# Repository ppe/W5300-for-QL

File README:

Hardware design and drivers for Sinclair QL experimental ethernet card.

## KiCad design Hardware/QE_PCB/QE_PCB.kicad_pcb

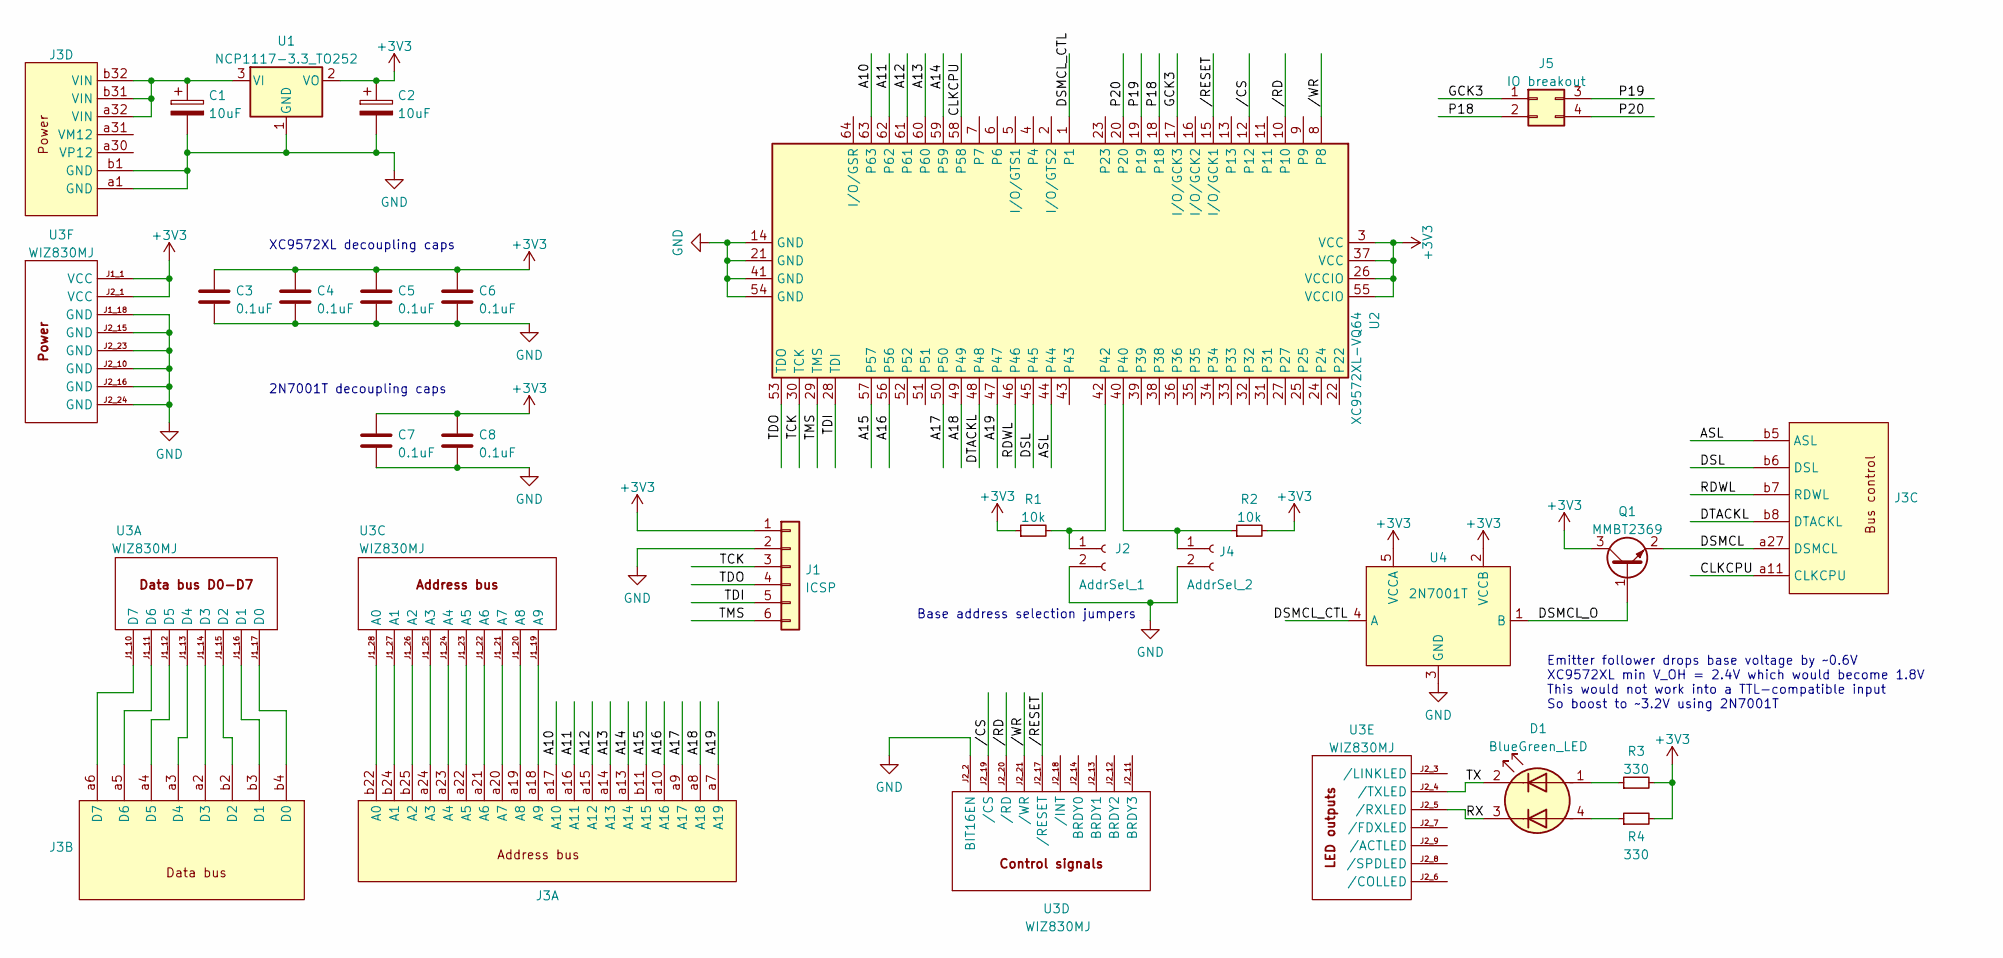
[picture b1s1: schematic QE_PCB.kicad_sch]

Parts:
C1, C2: 10uF; CP_EIA-6032-20_AVX-F_Pad2.25x2.35mm_HandSolder
C3, C4, C5, C6, C7, C8: 0.1uF; C_0603_1608Metric_Pad1.08x0.95mm_HandSolder
D1: BlueGreen_LED; LED_Dual_BG_2.0x1.25_Kingbright
J1: ICSP; PinHeader_1x06_P2.54mm_Vertical
J2: AddrSel_1; PinHeader_1x02_P2.54mm_Vertical
J3: Expansion_connector; DIN41612_B_2x32_Female_Horizontal_THT
J4: AddrSel_2; PinHeader_1x02_P2.54mm_Vertical
J5: IO breakout; PinHeader_1x04_P2.54mm_Vertical
Q1: MMBT2369; SOT-23
R1, R2: 10k; R_0805_2012Metric_Pad1.20x1.40mm_HandSolder
R3, R4: 330; R_0805_2012Metric_Pad1.20x1.40mm_HandSolder
U1: NCP1117-3.3_TO252; NCP1117 TO-252-2
U2: XC9572XL-VQ64; TQFP-64_10x10mm_P0.5mm
U3: WIZ830MJ
U4: 2N7001T; SOT-353_SC-70-5_Handsoldering

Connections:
+3V3: C2.1, C3.1, C4.1, C5.1, C6.1, C7.1, C8.1, J1.1, Q1.3 (C), R1.1, R2.2, R3.2, R4.2, U1.2 (VO), U2.3 (VCC), U2.26 (VCCIO), U2.37 (VCC), U2.55 (VCCIO), U3.J1_1 (VCC), U3.J2_1 (VCC), U4.2 (VCCB), U4.5 (VCCA)
/A10: J3.a17 (A10), U2.63
/A11: J3.a16 (A11), U2.62
/A12: J3.a15 (A12), U2.61
/A13: J3.a14 (A13), U2.60
/A14: J3.a13 (A14), U2.59
/A15: J3.b11 (A15), U2.57
/A16: J3.a10 (A16), U2.56
/A17: J3.a9 (A17), U2.50
/A18: J3.a8 (A18), U2.49
/A19: J3.a7 (A19), U2.47
/ASL: J3.b5 (ASL), U2.44
/CLKCPU: J3.a11 (CLKCPU), U2.58
/DSL: J3.b6 (DSL), U2.45
/DSMCL: J3.a27 (DSMCL), Q1.2 (E)
/DSMCL_CTL: U2.1, U4.4 (A)
/DSMCL_O: Q1.1 (B), U4.1 (B)
/DTACKL: J3.b8 (DTACKL), U2.48
/GCK3: J5.1, U2.17 (I/O/GCK3)
/P18: J5.2, U2.18
/P19: J5.3, U2.19
/P20: J5.4, U2.20
/RDWL: J3.b7 (RDWL), U2.46
/RX: D1.3 (K2), U3.J2_5 (/RXLED)
/TCK: J1.3, U2.30 (TCK)
/TDI: J1.5, U2.28 (TDI)
/TDO: J1.4, U2.53 (TDO)
/TMS: J1.6, U2.29 (TMS)
/TX: D1.2 (K1), U3.J2_4 (/TXLED)
//CS: U2.12, U3.J2_19 (/CS)
//RD: U2.10, U3.J2_20 (/RD)
//RESET: U2.15 (I/O/GCK1), U3.J2_17 (/RESET)
//WR: U2.8, U3.J2_21 (/WR)
GND: C1.2, C2.2, C3.2, C4.2, C5.2, C6.2, C7.2, C8.2, J1.2, J2.2, J3.a1 (GND), J3.b1 (GND), J4.2, U1.1 (GND), U2.14 (GND), U2.21 (GND), U2.41 (GND), U2.54 (GND), U3.J1_18 (GND), U3.J2_2 (BIT16EN), U3.J2_10 (GND), U3.J2_15 (GND), U3.J2_16 (GND), U3.J2_23 (GND), U3.J2_24 (GND), U4.3 (GND)
unnamed: C1.1, J3.a32 (VIN), J3.b31 (VIN), J3.b32 (VIN), U1.3 (VI)
unnamed: D1.1 (A1), R3.1
unnamed: D1.4 (A2), R4.1
unnamed: J2.1, R1.2, U2.42
unnamed: J3.a2 (D3), U3.J1_14 (D3)
unnamed: J3.a3 (D4), U3.J1_13 (D4)
unnamed: J3.a4 (D5), U3.J1_12 (D5)
unnamed: J3.a5 (D6), U3.J1_11 (D6)
unnamed: J3.a6 (D7), U3.J1_10 (D7)
unnamed: J3.a18 (A9), U3.J1_19 (A9)
unnamed: J3.a19 (A8), U3.J1_20 (A8)
unnamed: J3.a20 (A7), U3.J1_21 (A7)
unnamed: J3.a21 (A6), U3.J1_22 (A6)
unnamed: J3.a22 (A5), U3.J1_23 (A5)
unnamed: J3.a23 (A4), U3.J1_24 (A4)
unnamed: J3.a24 (A3), U3.J1_25 (A3)
unnamed: J3.b2 (D2), U3.J1_15 (D2)
unnamed: J3.b3 (D1), U3.J1_16 (D1)
unnamed: J3.b4 (D0), U3.J1_17 (D0)
unnamed: J3.b22 (A0), U3.J1_28 (A0)
unnamed: J3.b24 (A1), U3.J1_27 (A1)
unnamed: J3.b25 (A2), U3.J1_26 (A2)
unnamed: J4.1, R2.1, U2.40

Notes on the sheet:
Emitter follower drops base voltage by ~0.6V XC9572XL min V_OH = 2.4V which would become 1.8V This would not work into a TTL-compatible input So boost to ~3.2V using 2N7001T
XC9572XL decoupling caps
Base address selection jumpers
2N7001T decoupling caps

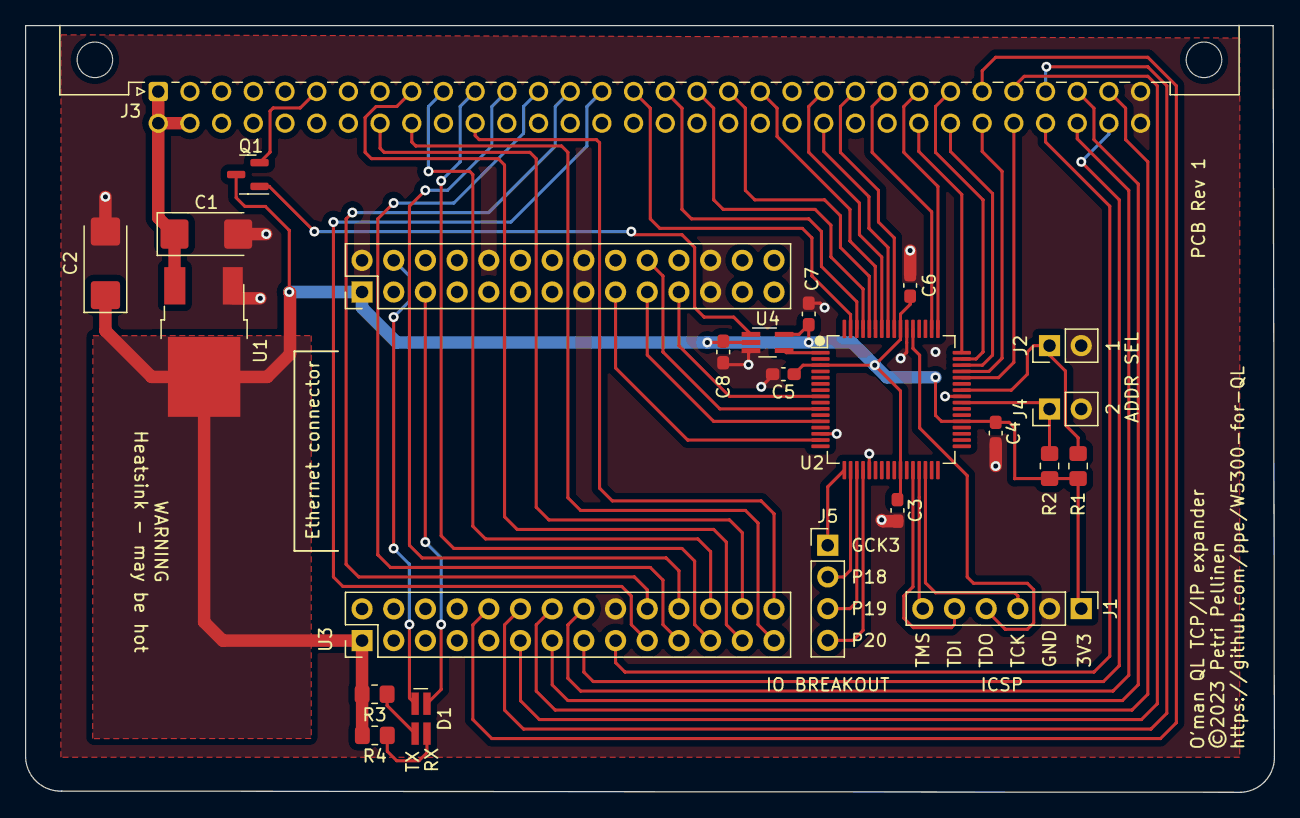
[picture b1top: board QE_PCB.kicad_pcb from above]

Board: 2 copper layers, 100.1 x 61.5 mm, 23 parts (0 on the bottom side), 57 nets.

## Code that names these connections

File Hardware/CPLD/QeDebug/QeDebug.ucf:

#PACE: Start of Constraints generated by PACE

#PACE: Start of PACE I/O Pin Assignments
NET "address<0>"  LOC = "P6" | BUFG = DATA_GATE ; 
NET "address<1>"  LOC = "P5" | BUFG = DATA_GATE ; 
NET "address<2>"  LOC = "P4"  ; 
NET "address<3>"  LOC = "P3"  ; 
NET "address<4>"  LOC = "P2"  ; 
NET "address<5>"  LOC = "P1"  ; 
NET "address<6>"  LOC = "P44"  ; 
NET "address<7>"  LOC = "P43"  ; 
NET "address<8>"  LOC = "P42"  ; 
NET "address<9>"  LOC = "P40"  ; 
NET "asl"  LOC = "P34"  ; 
NET "clk"  LOC = "P7" | BUFG = CLK  ;
NET "dbdir"  LOC = "P39"  ; 
NET "dbenl"  LOC = "P28"  ; 
NET "dsl"  LOC = "P33"  ; 
NET "dsmcl"  LOC = "P9"  ; 
NET "dtackl"  LOC = "P37"  ; 
NET "rdwl"  LOC = "P35"  ; 
NET "wizcsl"  LOC = "P26"  ; 
NET "wizrdl"  LOC = "P18"  ; 
NET "wizrstl"  LOC = "P20"  ; 
NET "wizwrl"  LOC = "P24"  ; 

#PACE: Start of PACE Area Constraints

#PACE: Start of PACE Prohibit Constraints

#PACE: End of Constraints generated by PACE

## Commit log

2011-02-27 Initial version (work in progress) of the DNS name resolver
2011-02-28 Initial import of W5300 specific code and start of device driver
2011-03-01 Driver name comparison work. Added the missing constatnts file
2011-03-01 Testing.
2011-03-01 Added number detection logic.
2011-03-02 Added a routine to test and read a byte value from string.
2011-03-02 Split test code to separate file
2011-03-02 Added an ip address parsing function.
2011-03-08 Generalized number parser. Replaced byte parser with new implementation.
2011-03-08 Added driver name parser that recognizes udp driver names with a numeric ip address and port
2011-03-20 Added nslookup superbasic extension. Currently it only creates a buffer that contains the dns query message.
2011-03-20 Added socket open code to socket layer
2012-01-19 WIP on prototype circuit board
2012-01-20 Initial (old) version of CPLD design files.
2012-01-20 Added ISP header and its connections to XC9536.
2012-02-22 First working version of nslookup.
2012-02-22 Restructured code to be more readable. Actual lookup refactored to be a standalone function.
2012-02-22 Extracted a separate resolver module.
2012-02-22 Ntpdate v1 without time zone support.
2012-02-22 Added missing free for malloc.
2012-02-26 First successful TCP test.
2012-02-27 Simplified version of address control for debugging purposes.
2012-02-27 Added Xilinx ISE ignores.
2012-09-18 Added a short project description.
2014-01-22 Add i2c and spi test code to debug project.
2014-01-23 wget_c: Modified server IP address.
2014-01-23 Add pseudocode for wget http header parsing.
2014-01-23 Change base address of w5300 address space.
2014-01-23 Add Eagle 6.4 schematics for the prototype adapter.
2014-01-23 Add library for the 3.3V regulator part used on the prototype board.
2014-01-23 Added comments to parser for better readability.
2014-01-24 Add stub for reading and resolving host name if no ip address given.
2014-01-25 Added hostname extraction routine to use for resolver call.
2014-01-26 Add LF line ending policy to .gitattributes.
2014-01-26 Fix syntax.
2014-01-26 Change include file device name to be parameterized.
2014-01-27 Fix return code for open call when driver name does not match.
2014-01-27 Fix driver name pointer on return from host name parse.
2014-03-26 Refactor driver name parsing code.
2014-04-02 Refactor address to dns format translation and add test harness.
2014-04-02 Add expectation verification to resolver test.
2014-04-05 Resolver: query buffers are now correctly populated.
2014-04-05 Resolver: add function to skip over names
2014-04-05 Resolver: add parse ip from response packet.
2014-10-19 Add initial version of SuperBASIC monitor program to examine status of W5300
2014-10-20 fix wrong function call in dst mac display
2014-11-17 Change address range to 2000 and remove address select.
2014-11-17 Remove ASL gating and rely on DSL instead.
2014-11-17 Change base addressess to C8000 (card) and C9000 (reset)
2014-11-17 Set output slew rate to slow
2014-11-17 Fix W5300 reset logic and add test for it.
2014-11-17 Fix gating, ack and dsmcl logic.
2014-11-17 Fix misunderstood timing and signalling for W5300. Best version so far
2014-11-17 Change gating: synchronize with clk to comply with 68k bus cycle specification.
2014-11-18 Resolver gethostbyname first checks if the host string is a dotted ip address.
2014-11-20 WIP http_client send and recv works, resp parsing broken
    Lots of other string handling broken also.
2014-12-01 WIP on http_client. Succesful receive of small text file.
2014-12-01 Rudimentary W5300 monitor basic program. Requires TK2.
2014-12-06 Remove test printf.
2014-12-06 wget: initial set of files
2014-12-09 wget: first working version
2014-12-31 WIP: start working on new version of driver
2015-01-06 Add memory allocation for channel open/close.
2015-01-07 QE_UNLOAD unloads driver and releases allocated heap.
2015-01-08 Add stub function for nslookup keyword in driver
2015-01-09 Add parameter handling to nslookup$ function.
2015-01-09 Change odd/even test in nslookup$
2015-01-09 Change way to clear A0.
2015-01-11 Stub trap #3 handler for gethostbyname.
2015-01-11 Refactor: extract get_driver_info helper function to use from keywords.
2015-01-11 add parameter validation to nslookup$ function, remove debug print to #0.
2015-01-11 Refactor get_driver_info: extract open/close routines for sck_ channel.
2015-01-11 Add to NSLOOKUP$: copy parameter to driver temporary buffer.
2015-01-11 Add user heap initialization to driver init.
2015-01-11 Change NSLOOKUP$: copy parameter to user heap block instead of static buffer.
2015-01-12 Change NSLOOKUP$: use LINK and frame pointer for local variable storage.
2015-01-13 remove old code. fix keyword table because of long extension names.
2015-01-13 NSLOOKUP$: add heap allocation for temporary struct hostent.
2015-01-13 NSLOOKUP$: fix heap allocation block size bug.
2015-01-13 NSLOOKUP$: fix bug clearing maths heap on exit Bug came up on Minerva, D2 is added to BV_RIP but the high word of the register may have rubbish in it thus mangling the maths stack.
2015-01-14 NSLOOKUP$: add cleanup code when hostent alloc fails.
2015-01-14 Refactor get_driver_info, pull out open/close SCK_ channel.
2015-01-14 NSLOOKUP$ refactor error and exit handling.
2015-01-14 NSLOOKUP$: add call to gethostbyname
2015-01-14 NSLOOKUP$ fix user heap allocation and pointer bug.
2015-01-15 gethostbyname: add static stub implementation that partially fills the struct hostent.
2015-01-15 gethostbyname: populate address family and bytes per address fields in struct hostent
2015-01-16 WIP: add inet_ntoa call.
2015-01-17 inet_ntoa impelementation
2015-01-17 nslookup$ use results from gethostbyname. TODO: change stack-based frame pointer to a user heap based one.
2015-01-18 Fix ntoa bug, channel id was not preserved in a0 through the call.
2015-01-18 NSLOOKUP$: fix return value handling on minerva.
2015-01-18 Add stub inet_aton implementation.
2015-01-18 inet_aton: add call to read ip address.
2015-01-19 gethostbyname: for an ip address, return a hostent with address as hostname and ip.
2015-01-20 gethostbyname: test user heap allocation from within the io handler.
2015-01-20 gethostbyname: create DNS query buffer and release it.
2015-01-21 gethostbyname: add dummy fixed dns response packet and call to parse it.
2015-01-22 dns response parser: fix answer skip logic
2015-01-22 parse dns response: fix syntax errors
2015-01-22 gethostbyname: return answer from captured packet.
2015-01-22 WIP: proper parsing of DNS response packet.
2015-01-23 WIP parse dns response: process stack now sets up CNAME and A tables in struct hostent.
2015-01-24 dns response parser: add copy hostname from first A resource.
2015-01-25 resolv: pick ip addresses from dns response and populate them in struct hostent.
2015-01-25 nslookup$: pick first ip address from struct hostent as return value
2015-01-26 response parser: parse aliases into struct hostent
2015-01-26 response parser: remove trailing '.' from names and aliases.
2015-01-27 Add return value generation in dns response parsing.
2015-01-28 Add W5300 HW layer file and call HW init from driver init.
2015-01-29 driver init: initialize a socket reservation table in driver linkage block.
2015-01-29 gethostbyname: change local vars to use frame pointer in preparation for socket reservation code.
2015-01-29 gethostbyname: fix user heap deallocation bug.
2015-01-30 gethostbyname: add socket reservation to lookup
2015-01-30 gethostbyname: add release socket reservation.
2015-01-31 w5300: add open routine for UDP sockets. Support ERR_NC and continuation.
2015-02-01 gethostbyname and w5300 continuation mechanism WIP.
2015-02-01 Add socket close operation.
2015-02-01 Fix bug filling struct hostent when query address is an ip.
2015-02-01 Change function call name
2015-02-01 Close and release sockets when closing channel and/or starting new IO op on channel after timeout.
2015-02-02 Add stub sendto implementation.
2015-02-03 Add _list and _rel files to .gitignore to prepare for qmac assembler
2015-02-03 Change w5300_asm source to qmac assembler format.
2015-02-03 Add skeleton makefile for driver.
2015-02-04 Rename w5300 include file.
2015-02-04 Add make dependency to include file.
2015-02-04 Change resolv_asm to Qmac asm format.
2015-02-04 Makefile: add dependency to resolv_asm.
2015-02-04 Change parser_asm to Qmac asm format.
2015-02-04 Makefile: add dependency to parser_asm.
2015-02-05 Change driver_asm to qmac format.
2015-02-05 Makefile: add dependency to driver_asm
2015-02-05 Makefile: add linking instruction for driver target.
2015-02-05 Add linker _map files to .gitignore.
2015-02-06 Small makefile fix
2015-02-07 Add stub to set destination for a socket.
2015-02-08 Fix the routine to write bytes to a socket.
2015-02-08 Refactor w5300-specific sendto code into w5300 module.
2015-02-08 WIP on HW layer sendto implementation.
2015-02-09 Add logic to open a UDP socket (without destination info).
2015-02-09 Add sendto implementation scaffolding to IOSS layer.
2015-02-10 Fix W5300 buffer write.
2015-02-10 Fix socket close sending wrong command to W5300.
2015-02-11 Fix socket number parameter in socket close.
2015-02-11 Fix sendok check logic in sendto.
2015-02-12 Add stub for recvfrom implementation.
2015-02-13 WIP: add recvfrom w5300 implementation.
2015-02-14 WIP on read bytes from socket.
2015-02-15 WIP on recvfrom: fix bug in odd-byte reads.
2015-02-15 recvfrom: add unaligned target buffer logic.
2015-02-16 add recvfrom parameter check
2015-02-17 Add received bytes # check to recvfrom.
2015-02-18 add call to w5300 impelementation code from recvfrom.
2015-02-19 Add FIFO buffer copy to w5300 recvfrom implementation.
2015-02-19 W5300 recvfrom: mark the packet as received after copying through FIFO.
2016-04-21 Ignore _o files
2016-04-21 Add (partly broken) prototype irc client
2016-04-21 Refactor driver to be hybrid c/asm driver
2016-11-10 Add gitattributes file to define file extensions for languages not automatically picked up by GitHub (probably due to non-standard file extension)
2016-11-10 gitattributes fix, move linguist-language definitions to root
2023-01-12 PCB Rev 1

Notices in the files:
Hardware/QE_PCB/QE_PCB.kicad_pcb:
©2023 Petri Pellinen
